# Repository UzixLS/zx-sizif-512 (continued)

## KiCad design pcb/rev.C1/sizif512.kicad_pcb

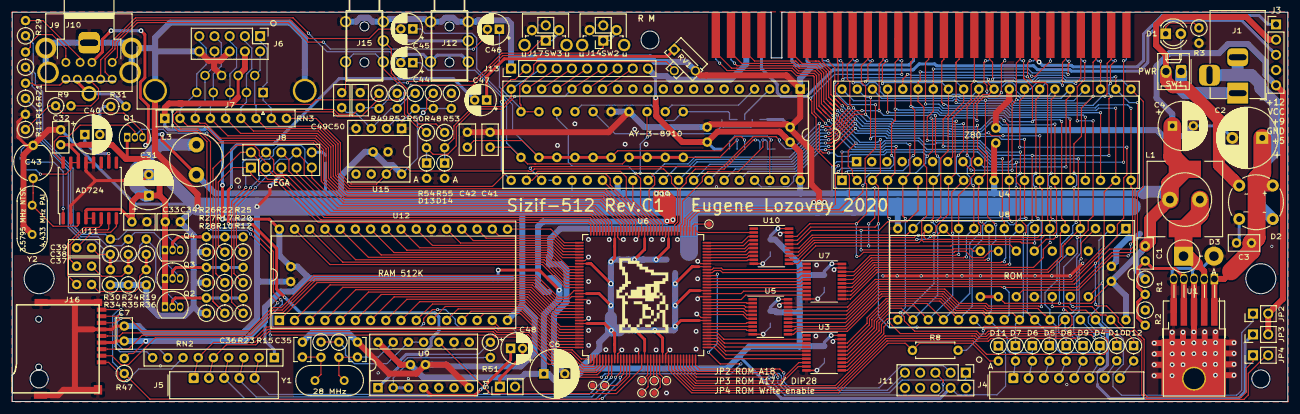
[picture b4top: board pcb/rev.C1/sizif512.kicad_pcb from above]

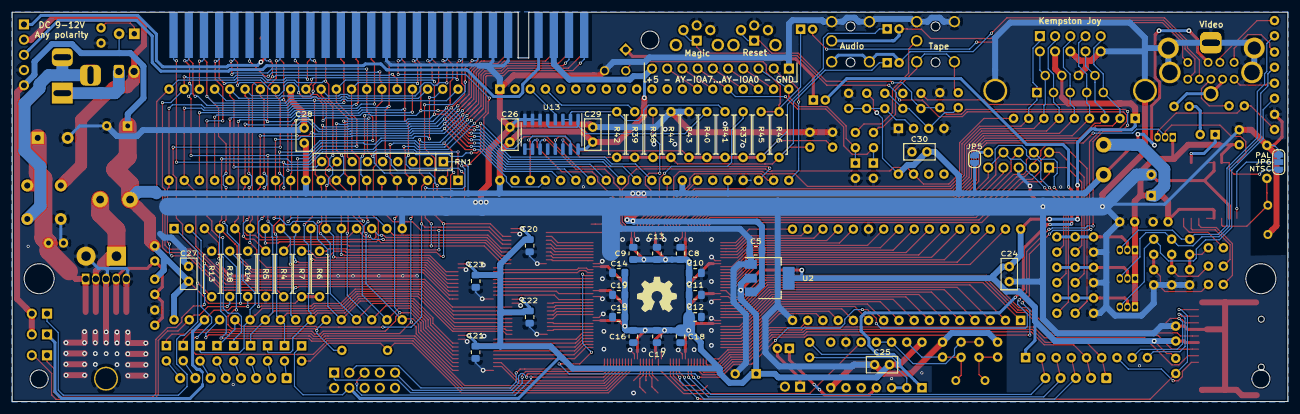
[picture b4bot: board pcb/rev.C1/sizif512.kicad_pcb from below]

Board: 2 copper layers, 213.0 x 65.0 mm, 186 parts (47 on the bottom side), 235 nets.

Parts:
C1: 15n; C_Disc_D5.0mm_W2.5mm_P2.50mm
C2: 470u/25V; CP_Radial_D10.0mm_P5.00mm
C3, C7, C24, C25, C26, C27, C28, C29, C30, C32, C33, C34, C37, C38, C39, C49, C50: 100n; C_Disc_D5.0mm_W2.5mm_P2.50mm
C4, C6, C31: 220u/16V; CP_Radial_D8.0mm_P3.50mm
C5, C8, C9, C10, C11, C12, C13, C14, C15, C16, C17, C19, C20, C21, C22, C23: 100n; C_0805_2012Metric_Pad1.15x1.40mm_HandSolder
C18: 10n; C_0805_2012Metric_Pad1.15x1.40mm_HandSolder
C35, C36: 22p; C_Disc_D3.8mm_W2.6mm_P2.50mm
C40: 220u/16V; CP_Radial_D6.3mm_P2.50mm
C41, C42: 4.7n; C_Disc_D5.0mm_W2.5mm_P2.50mm
C43: 30p; C_Trim_D6.3mm_P5.50mm
C44, C45, C46, C48: 10u/16V; CP_Radial_D5.0mm_P2.00mm
C47: 1u; CP_Radial_D5.0mm_P2.00mm
D1: LED; LED_D4.0mm
D2: 2W10; Diode_Bridge_Round_D10.0mm
D3: 1N5820; D_DO-201AD_P5.08mm_Vertical_AnodeUp
D4, D5, D6, D7, D8, D9, D10, D11, D12, D13, D14: BAT85; D_DO-35_SOD27_P2.54mm_Vertical_AnodeUp
H1, H2: MountingHole; MountingHole_5mm
H3, H4, H5: MountingHole; MountingHole_3mm
J1: DS-210; BarrelJack_Horizontal
J2: Conn_02x28_Row_Letter_First; ZX_EDGE
J3: PinHeader; PinHeader_1x05_P2.54mm_Vertical
J4: DS1020-08; FFC_FPC_1x08
J5: DS1020-05; FFC_FPC_1x05
J6, J8, J11: PinHeader; PinHeader_2x05_P2.54mm_Vertical
J7: DB9-M; DSUB-9_Male_Horizontal_P2.77x2.84mm_EdgePinOffset4.94mm_Hou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
J9: Mini-DIN-9; minidin-9
J10: RCJ-014; CUI_RCJ-01X-WIDE
J12, J15: PJ-313
J13: PinHeader; PinHeader_1x10_P2.54mm_Vertical
J14, J17: PinHeader; PinHeader_2x01_P2.54mm_Vertical
J16: MEM2055-00-190-01-A; GCT-MEM2055-00-190-01-A
JP2, JP3, JP4: Jumper; PinHeader_1x02_P2.54mm_Vertical
JP5: SolderJumper_2_Open; SolderJumper-2_P1.3mm_Open_RoundedPad1.0x1.5mm
JP6: Jumper_3_Bridged12; SolderJumper-3_P1.3mm_Bridged12_RoundedPad1.0x1.5mm_NumberL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
L1: 68uH/2A; L_Radial_D8.7mm_P5.00mm_Fastron_07HCP
L2: 68uH/2A; L_12x12mm_H8mm
L3: 220u/0.2A; L_Radial_D8.7mm_P5.00mm_Fastron_07HCP
LOGO1: graphic; black-mage2
LOGO2: Logo_Open_Hardware_Small; OSHW-Symbol_6.7x6mm_SilkScreen
LS1: PinHeader; PinHeader_1x02_P2.54mm_Vertical
Q1, Q2, Q3, Q4: BC549B; TO-92_Inline
R1, R12, R20, R25: 3k; R_Axial_DIN0207_L6.3mm_D2.5mm_P2.54mm_Vertical
R2, R48, R53: 1k; R_Axial_DIN0207_L6.3mm_D2.5mm_P2.54mm_Vertical
R3: 470; R_Axial_DIN0207_L6.3mm_D2.5mm_P2.54mm_Vertical
R4, R8: 470; R_Axial_DIN0207_L6.3mm_D2.5mm_P7.62mm_Horizontal
R5, R13, R14, R18: 10k; R_Axial_DIN0207_L6.3mm_D2.5mm_P7.62mm_Horizontal
R6, R7, R41, R42: 2k; R_Axial_DIN0207_L6.3mm_D2.5mm_P7.62mm_Horizontal
R9, R11, R23: 270; R_Axial_DIN0207_L6.3mm_D2.5mm_P2.54mm_Vertical
R10, R17, R22, R26, R27, R28: 1.5k; R_Axial_DIN0207_L6.3mm_D2.5mm_P2.54mm_Vertical
R15, R52: 1M; R_Axial_DIN0207_L6.3mm_D2.5mm_P2.54mm_Vertical
R16, R19, R21, R24, R29, R30: 68; R_Axial_DIN0207_L6.3mm_D2.5mm_P2.54mm_Vertical
R31, R34, R35, R36: 75; R_Axial_DIN0207_L6.3mm_D2.5mm_P2.54mm_Vertical
R37, R38, R39, R40, R43, R44: 1k; R_Axial_DIN0207_L6.3mm_D2.5mm_P7.62mm_Horizontal
R45, R46: 4.7k; R_Axial_DIN0207_L6.3mm_D2.5mm_P7.62mm_Horizontal
R47, R50, R51, R54, R55: 10k; R_Axial_DIN0207_L6.3mm_D2.5mm_P2.54mm_Vertical
R49: 100k; R_Axial_DIN0207_L6.3mm_D2.5mm_P2.54mm_Vertical
RN1, RN2, RN3: 10k; R_Array_SIP9
RV1: RM063 47k; Potentiometer_Runtron_RM-063_Horizontal
SW1: Jumper; Molex_KK-254_AE-6410-02A_1x02_P2.54mm_Vertical
SW2, SW3: Button THT; SW_Tactile_SPST_Angled_PTS645Vx83-2LFS
TP1, TP2, TP3, TP4, TP5, TP6, TP7, TP8: TestPoint; TestPoint_Pad_D1.0mm
U1: LM2596T-ADJ; TO-220-263-5_Horizontal_TabDown
U2: AMS1117-3.3; SOT-223-3_TabPin2
U3, U5, U7, U10: SN74CB3T3245PW; TSSOP-20_4.4x6.5mm_P0.65mm
U4: Z84C0010PEC; DIP-40_W15.24mm_Socket
U6: EPM1270T144; LQFP-144_20x20mm_P0.5mm
U8: SST39SF040; DIP-32_W15.24mm_Socket
U9: 74HCU04; DIP-14_W7.62mm_Socket
U11: AD724; SOIC-16W_7.5x10.3mm_P1.27mm
U12: AS6C4008-55PCN; DIP-32_W15.24mm_Socket
U13: 74HCT4053D; SOIC-16_3.9x9.9mm_P1.27mm
U14: AY-3-8910; DIP-40_W15.24mm_Socket
U15: LM311N; DIP-8_W7.62mm_Socket
Y1: 28 MHz; Crystal_HC49-U_Vertical
Y2: 4.433 MHz; Crystal_HC49-U_Vertical

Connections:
+3V3: C6.1, C7.2, C8.1, C9.1, C10.1, C11.1, C12.1, C13.1, C14.1, C15.1, C16.1, C17.1, C18.1, C19.1, C20.1, C21.1, C22.1, C23.1, C24.2, C25.2, D11.1, J6.4, J7.7, J11.4, J16.4, R47.2, R49.1, RN2.1, RN3.1, U2.2, U3.20, U5.20, U6.9, U6.19, U6.25, U6.46, U6.56, U6.64, U6.82, U6.90, U6.100, U6.116, U6.126, U6.136, U7.20, U9.14, U10.20, U12.32
+5V: C1.1, C4.1, C5.2, C26.2, C27.2, C28.2, C29.2, C30.2, D1.2, J2.A3, J3.5, J9.2, J13.10, JP2.2, JP3.2, JP5.1, L1.2, L2.2, L3.1, R1.1, R6.1, R7.2, R18.1, R48.1, RN1.1, U2.3, U4.11, U8.32, U13.16, U14.25, U14.28, U14.40, U15.8
+5VA: C31.1, C32.2, C33.2, C34.2, JP6.3, L3.2, Q1.1, Q2.1, Q3.1, Q4.1, U11.4, U11.5, U11.14, U11.15
+9V: J2.A4, J3.3
+12V: J2.B22, J3.1
/A0: J2.A9, U4.30, U7.18, U8.12
/A1: J2.A10, U4.31, U7.17, U8.11
/A2: J2.A11, U4.32, U7.16, U8.10
/A3: J2.A12, U4.33, U7.15, U8.9
/A4: J2.A24, U4.34, U7.14, U8.8
/A5: J2.A23, U4.35, U8.7, U10.12
/A6: J2.A22, U4.36, U7.13, U8.6
/A7: J2.A21, U4.37, U7.12, U8.5
/A8: D4.1, J2.B26, U4.38, U5.13, U8.27
/A9: D5.1, J2.A27, U4.39, U5.12, U8.26
/A10: D6.1, J2.B27, U3.18, U4.40, U8.23
/A11: D7.1, J2.A28, U4.1, U5.11, U8.25
/A12: D8.1, J2.A2, U4.2, U7.11, U8.4
/A13: D9.1, J2.B2, U4.3, U8.28, U10.17
/A14: D10.1, J2.A1, U3.11, U4.4
/A15: D12.1, J2.B1, U3.13, U4.5
/AY_ABC: U6.78, U13.9, U13.10
/AY_BC1: U6.86, U14.29
/AY_BDIR: U6.89, U14.27
/AY_CLK: U6.88, U14.22
/AY_MONO: U6.79, U13.11
/Blue0: J8.8, R25.1, U6.102
/Blue1: J8.1, R22.1, U6.108
/CLK28: U6.18, U9.10
/CLKCPU: R6.2, U4.6, U10.16
/Csync: Q1.2, U6.98, U11.16
/D0: J2.B6, U4.14, U8.13, U10.13, U14.37
/D1: J2.B7, U4.15, U8.14, U10.14, U14.36
/D2: J2.B8, U4.12, U8.15, U10.15, U14.35
/D3: J2.B11, U3.12, U4.8, U8.17, U14.34
/D4: J2.B12, U3.14, U4.7, U8.18, U14.33
/D5: J2.B10, U3.15, U4.9, U8.19, U14.32
/D6: J2.B9, U3.16, U4.10, U8.20, U14.31
/D7: J2.B3, U3.17, U4.13, U8.21, U14.30
/Green0: J8.9, R20.1, U6.101
/Green1: J8.2, R17.1, U6.107
/Hsync: J8.7, U6.103
/KA8: D4.2, J4.6
/KA9: D5.2, J4.3
/KA10: D6.2, J4.2
/KA11: D7.2, J4.1
/KA12: D8.2, J4.4
/KA13: D9.2, J4.5
/KA14: D10.2, J4.7
/KA15: D12.2, J4.8
/KD0: J5.1, RN2.6, U6.4
/KD1: J5.2, RN2.5, U6.5
/KD2: J5.3, RN2.4, U6.11
/KD3: J5.4, RN2.3, U6.8
/KD4: J5.5, RN2.2, U6.7
/RA14: U6.30, U8.29
/RA15: U6.29, U8.3
/RA16: U6.28, U8.2
/RX: C49.2, J15.T, R54.1
/Red0: J8.4, R12.1, U6.105
/Red1: J8.3, R10.1, U6.106
/SD_CD: J16.9, R47.1, U6.12
/SD_CS: J16.2, U6.3
/SD_DAT1: J16.8, RN2.9
/SD_DAT2: J16.1, RN2.7
/SD_MISO: J16.7, RN2.8, U6.125
/SD_MOSI: J16.3, U6.129
/SD_SCK: J16.5, U6.127
/SND_DAC_L: R38.2, U6.84
/SND_DAC_R: R37.2, U6.85
/SND_L: C44.2, J9.8, J12.T
/SND_MONO: C46.2, J9.6
/SND_R: C45.2, J9.9, J12.R
/TAPE_IN0: RN3.9, U6.80, U15.7
/TCK: J11.1, U6.35
/TDI: J11.9, U6.34
/TDO: J11.3, U6.36
/TMS: J11.5, U6.33
/TX: J15.R, R55.1
/VA0: U6.143, U12.12
/VA1: U6.142, U12.11
/VA2: U6.141, U12.10
/VA3: U6.140, U12.9
/VA4: U6.139, U12.8
/VA5: U6.138, U12.7
/VA6: U6.137, U12.6
/VA7: U6.134, U12.5
/VA8: U6.120, U12.27
/VA9: U6.119, U12.26
/VA10: U6.114, U12.23
/VA11: U6.118, U12.25
/VA12: U6.133, U12.4
/VA13: U6.121, U12.28
/VA14: U6.132, U12.3
/VA15: U6.124, U12.31
/VA16: U6.131, U12.2
/VA17: U6.130, U12.1
/VA18: U6.123, U12.30
/VD0: U6.144, U12.13
/VD1: U6.1, U12.14
/VD2: U6.2, U12.15
/VD3: U6.109, U12.17
/VD4: U6.110, U12.18
/VD5: U6.111, U12.19
/VD6: U6.112, U12.20
/VD7: U6.113, U12.21
/VID_B: J9.1, R29.2
/VID_COMP: J9.4, J10.1, R31.2
/VID_G: J9.3, R21.2
/VID_R: J9.7, R16.2
/VID_SYNC: J9.5, R9.2
/Vsync: J8.6, U6.104
/xA0: U6.63, U7.2
/xA1: U6.62, U7.3
/xA2: U6.60, U7.4
/xA3: U6.59, U7.5
/xA4: U6.58, U7.6
/xA5: U6.67, U10.8
/xA6: U6.57, U7.7
/xA7: U6.55, U7.8
/xA8: U5.7, U6.45
/xA9: U5.8, U6.44
/xA10: U3.2, U6.42
/xA11: U5.9, U6.43
/xA12: U6.53, U7.9
/xA13: U6.72, U10.3
/xA14: U3.9, U6.31
/xA15: U3.7, U6.37
/xCLKCPU: U6.71, U10.4
/xD0: U6.68, U10.7
/xD1: U6.69, U10.6
/xD2: U6.70, U10.5
/xD3: U3.8, U6.32
/xD4: U3.6, U6.38
/xD5: U3.5, U6.39
/xD6: U3.4, U6.40
/xD7: U3.3, U6.41
/~BUSACK: J2.A26, U4.23
/~BUSRQ: J2.A19, RN1.9, U4.25
/~CLKCPU: J2.A8, R7.1, U10.18
/~HALT: J2.B15, U4.18
/~INT: J2.B13, U4.16, U6.77
/~IORQ: J2.B17, R4.2, U4.20
/~IORQGE: J2.A13, R4.1, U10.11
/~JOY_B1: J6.2, J7.6, RN3.7, U6.91
/~JOY_B2: J6.8, J7.9, RN3.3, U6.96
/~JOY_B3: J6.9, J7.5, RN3.2, U6.97
/~JOY_DOWN: J6.3, J7.2, RN3.6, U6.93
/~JOY_LEFT: J6.5, J7.3, RN3.5, U6.94
/~JOY_RIGHT: J6.7, J7.4, RN3.4, U6.95
/~JOY_UP: J6.1, J7.1, RN3.8, U6.87
/~M1: J2.B24, U4.27, U5.14
/~MREQ: J2.B16, U4.19, U5.18
/~NMI: J2.B14, U4.17, U6.76
/~RD: J2.B18, RN1.7, U4.21, U5.15, U8.24
/~RFSH: J2.B25, U4.28, U5.17
/~ROMCS: D11.2, R8.2, U6.27
/~ROMCSB: J2.A25, R8.1, U8.22
/~RSTCPU: J2.A20, R5.1, U4.26, U6.75, U14.23
/~VRD: U6.117, U12.24
/~VWR: U6.122, U12.29
/~WAIT: J2.B21, RN1.8, U4.24
/~WR: J2.B19, JP4.1, U4.22, U5.16
/~xCLKCPU_IO73: U6.73, U10.2
/~xIORQGE: U6.66, U10.9
/~xM1: U5.6, U6.48
/~xMREQ: U5.2, U6.52
/~xRD: U5.5, U6.49
/~xRFSH: U5.3, U6.51
/~xWR: U5.4, U6.50
GND: C2.2, C3.2, C4.2, C5.1, C6.2, C7.1, C8.2, C9.2, C10.2, C11.2, C12.2, C13.2, C14.2, C15.2, C16.2, C17.2, C18.2, C19.2, C20.2, C21.2, C22.2, C23.2, C24.1, C25.1, C26.1, C27.1, C28.1, C29.1, C30.1, C31.2, C32.1, C33.1, C34.1, C35.1, C36.1, C41.2, C42.2, C43.2, C50.1, D2.1, D3.2, D13.2, D14.2, J2.A6, J2.A7, J2.A14, J3.4, J6.6, J6.10, J7.0, J7.8, J8.5, J9.0, J10.2, J11.2, J11.10, J12.S, J13.1, J14.2, J15.S, J16.6, J16.10, J17.2, JP6.1, LS1.2, R2.1, R3.2, R5.2, R11.2, R13.1, R14.1, R26.1, R27.1, R28.1, R34.1, R35.1, R36.1, R43.2, R44.2, R52.1, R53.1, RV1.3, SW2.1, SW3.1, U1.3, U1.5, U2.1, U3.10, U3.19, U4.29, U5.10, U5.19, U6.10, U6.17, U6.26, U6.47, U6.54, U6.65, U6.83, U6.92, U6.99, U6.115, U6.128, U6.135, U7.10, U7.19, U8.16, U9.5, U9.7, U9.9, U10.10, U10.19, U11.2, U11.12, U11.13, U12.16, U12.22, U13.6, U13.7, U13.8, U14.1, U14.24, U15.1, U15.4, Y2.2
unnamed: C1.2, R1.2, R2.2, U1.4
unnamed: C2.1, C3.1, D2.3, U1.1
unnamed: C35.2, R15.2, U9.13, Y1.2
unnamed: C36.2, R23.2, Y1.1
unnamed: C37.1, R19.1, R36.2
unnamed: C37.2, U11.6
unnamed: C38.1, R24.1, R35.2
unnamed: C38.2, U11.7
unnamed: C39.1, R30.1, R34.2
unnamed: C39.2, U11.8
unnamed: C40.1, U11.10
unnamed: C40.2, R31.1
unnamed: C41.1, C44.1, R38.1, R39.1, R42.1, R44.1, R46.1, U13.14
unnamed: C42.1, C45.1, R37.1, R40.1, R41.1, R43.1, R45.1, U13.13
unnamed: C43.1, U11.3, Y2.1
unnamed: C46.1, R45.2, R46.2, RV1.2
unnamed: C47.1, RV1.1
unnamed: C47.2, R51.1, U9.1
unnamed: C48.1, U9.4
unnamed: C48.2, LS1.1
unnamed: C49.1, R50.1, R52.2, U15.3
unnamed: D1.1, R3.1
unnamed: D2.2, J1.2, J1.3
unnamed: D3.1, L1.1, L2.1, U1.2
unnamed: D13.1, J13.7, R54.2, U14.16
unnamed: D14.1, J13.3, R55.2, U14.20
unnamed: J1.1, SW1.1
unnamed: J8.10, JP5.2
unnamed: J13.2, U14.21
unnamed: J13.4, U14.19
unnamed: J13.5, U14.18
unnamed: J13.6, U14.17
unnamed: J13.8, U14.15
unnamed: J13.9, U14.14
unnamed: JP2.1, R13.2, U8.1
unnamed: JP3.1, R14.2, U8.30
unnamed: JP4.2, R18.2, U8.31
unnamed: JP6.2, U11.1
unnamed: Q1.3, R9.1, R11.1
unnamed: Q2.2, R10.2, R12.2, R28.2
unnamed: Q2.3, R16.1, R19.2
unnamed: Q3.2, R17.2, R20.2, R27.2
unnamed: Q3.3, R21.1, R24.2
unnamed: Q4.2, R22.2, R25.2, R26.2
unnamed: Q4.3, R29.1, R30.2
unnamed: R15.1, R23.1, U9.11, U9.12
unnamed: R39.2, U14.4
unnamed: R40.2, U13.1, U13.5
unnamed: R41.2, R42.2, U13.2, U13.3
unnamed: R48.2, R50.2, R53.2, U15.2
unnamed: R51.2, U9.2, U9.3
unnamed: TP1.1, U6.74
unnamed: TP2.1, U6.13
unnamed: TP3.1, U6.14
unnamed: TP4.1, U6.20
unnamed: TP5.1, U6.21
unnamed: TP6.1, U6.22
unnamed: TP7.1, U6.23
unnamed: TP8.1, U6.24
unnamed: U13.4, U14.3
unnamed: U13.15, U14.38
VCC: D2.4, J3.2, SW1.2
~MAGIC: J14.1, SW2.2, U6.6
~RST: C50.2, J17.1, R49.2, SW3.2, U6.61

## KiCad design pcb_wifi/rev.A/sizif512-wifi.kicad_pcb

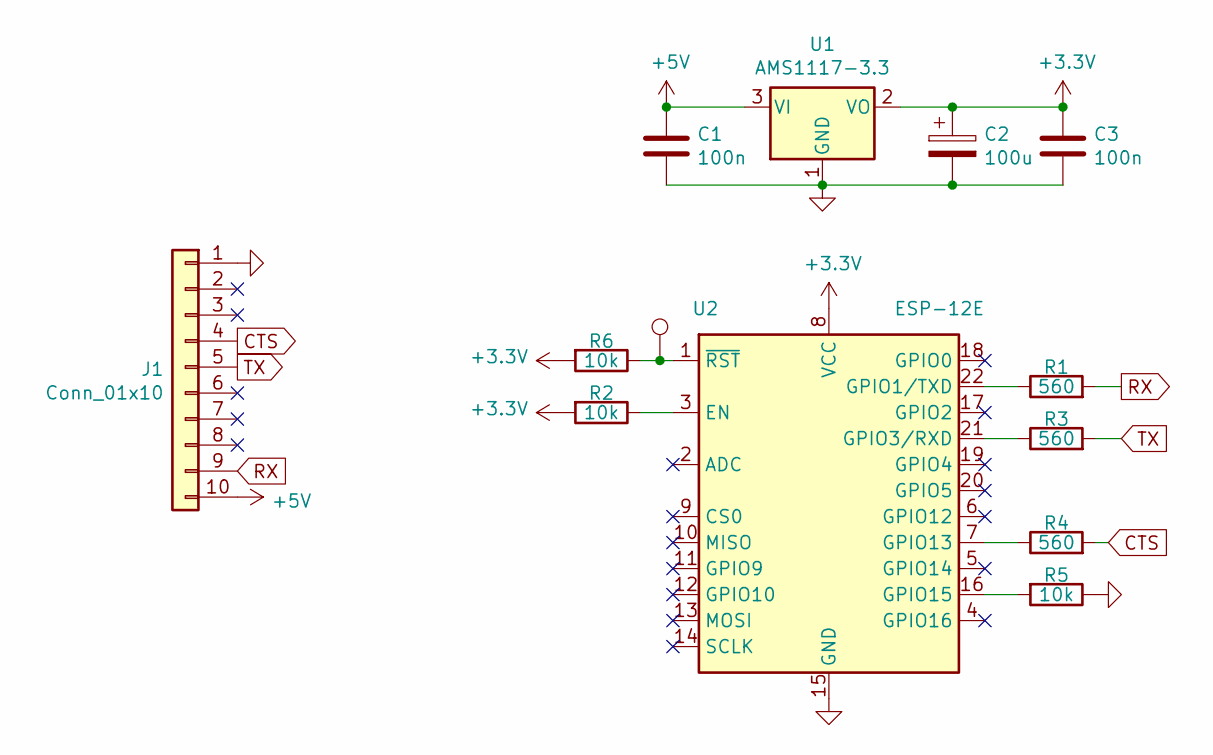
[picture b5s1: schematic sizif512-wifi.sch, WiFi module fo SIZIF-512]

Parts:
C1, C3: 100n; C_0805_2012Metric_Pad1.15x1.40mm_HandSolder
C2: 100u; C_2010_5025Metric_Pad1.52x2.65mm_HandSolder
J1: Conn_01x10; PinSocket_1x10_P2.54mm_Vertical
R1, R3, R4: 560; C_0805_2012Metric_Pad1.15x1.40mm_HandSolder
R2, R5, R6: 10k; C_0805_2012Metric_Pad1.15x1.40mm_HandSolder
TP1: TestPoint; Pin_D0.7mm_L6.5mm_W1.8mm_FlatFork
U1: AMS1117-3.3; SOT-223-3_TabPin2
U2: ESP-12E; ESP-12E_SMD

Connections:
+3V3: C2.1, C3.1, R2.2, R6.2, U1.2 (VO), U2.8 (VCC)
+5V: C1.1, J1.10, U1.3 (VI)
CTS: J1.4, R4.2
GND: C1.2, C2.2, C3.2, J1.1, R5.1, U1.1 (GND), U2.15 (GND)
unnamed: R1.1, U2.22 (GPIO1/TXD)
unnamed: R2.1, U2.3 (EN)
unnamed: R3.1, U2.21 (GPIO3/RXD)
unnamed: R4.1, U2.7 (GPIO13)
unnamed: R5.2, U2.16 (GPIO15)
unnamed: R6.1, TP1.1, U2.1 (~RST)
RX: J1.9, R1.2
TX: J1.5, R3.2

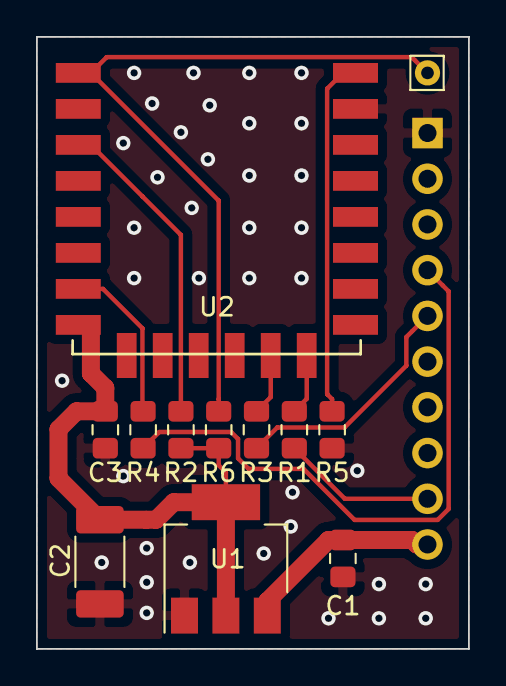
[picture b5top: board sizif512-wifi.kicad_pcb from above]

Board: 2 copper layers, 24.0 x 34.0 mm, 13 parts (1 on the bottom side), 12 nets.

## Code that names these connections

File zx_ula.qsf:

# -------------------------------------------------------------------------- #
#
# Copyright (C) 1991-2009 Altera Corporation
# Your use of Altera Corporation's design tools, logic functions 
# and other software and tools, and its AMPP partner logic 
# functions, and any output files from any of the foregoing 
# (including device programming or simulation files), and any 
# associated documentation or information are expressly subject 
# to the terms and conditions of the Altera Program License 
# Subscription Agreement, Altera MegaCore Function License 
# Agreement, or other applicable license agreement, including, 
# without limitation, that your use is for the sole purpose of 
# programming logic devices manufactured by Altera and sold by 
# Altera or its authorized distributors.  Please refer to the 
# applicable agreement for further details.
#
# -------------------------------------------------------------------------- #
#
# Quartus II
# Version 9.0 Build 235 06/17/2009 Service Pack 2 SJ Web Edition
# Date created = 08:15:12  April 28, 2019
#
# -------------------------------------------------------------------------- #
#
# Notes:
#
# 1) The default values for assignments are stored in the file:
#		zx_ula_assignment_defaults.qdf
#    If this file doesn't exist, see file:
#		assignment_defaults.qdf
#
# 2) Altera recommends that you do not modify this file. This
#    file is updated automatically by the Quartus II software
#    and any changes you make may be lost or overwritten.
#
# -------------------------------------------------------------------------- #


set_global_assignment -name FAMILY MAX3000A
set_global_assignment -name DEVICE "EPM3256ATC144-10"
set_global_assignment -name TOP_LEVEL_ENTITY zx_ula
set_global_assignment -name ORIGINAL_QUARTUS_VERSION "9.0 SP2"
set_global_assignment -name PROJECT_CREATION_TIME_DATE "08:15:12  APRIL 28, 2019"
set_global_assignment -name LAST_QUARTUS_VERSION "9.0 SP2"
set_global_assignment -name USE_GENERATED_PHYSICAL_CONSTRAINTS OFF -section_id eda_blast_fpga
set_global_assignment -name MAX7000_DEVICE_IO_STANDARD "3.3-V LVTTL"
set_location_assignment PIN_36 -to n_int
set_location_assignment PIN_29 -to n_iorq
set_location_assignment PIN_34 -to n_m1
set_location_assignment PIN_28 -to n_mreq
set_location_assignment PIN_27 -to n_rfsh
set_location_assignment PIN_6 -to n_vwr
set_location_assignment PIN_72 -to r
set_location_assignment PIN_127 -to rst_n
set_location_assignment PIN_60 -to tape_out
set_location_assignment PIN_25 -to va[16]
set_location_assignment PIN_30 -to va[15]
set_location_assignment PIN_31 -to va[14]
set_location_assignment PIN_11 -to va[13]
set_location_assignment PIN_12 -to va[12]
set_location_assignment PIN_14 -to va[11]
set_location_assignment PIN_15 -to va[10]
set_location_assignment PIN_16 -to va[9]
set_location_assignment PIN_18 -to va[8]
set_location_assignment PIN_8 -to va[7]
set_location_assignment PIN_5 -to va[6]
set_location_assignment PIN_2 -to va[5]
set_location_assignment PIN_1 -to va[4]
set_location_assignment PIN_10 -to va[1]
set_location_assignment PIN_9 -to va[0]
set_location_assignment PIN_39 -to vd[7]
set_location_assignment PIN_40 -to vd[6]
set_location_assignment PIN_38 -to vd[4]
set_location_assignment PIN_37 -to vd[2]
set_location_assignment PIN_32 -to vd[0]
set_global_assignment -name MISC_FILE "E:/ws/quartus/zx_ula/zx_ula.dpf"
set_global_assignment -name VERILOG_INPUT_VERSION SYSTEMVERILOG_2005
set_global_assignment -name VERILOG_SHOW_LMF_MAPPING_MESSAGES OFF
set_global_assignment -name MAX7000_OPTIMIZATION_TECHNIQUE AREA
set_global_assignment -name FMAX_REQUIREMENT "14.4 MHz"
set_global_assignment -name FMAX_REQUIREMENT "14.4 MHz" -section_id clk14
set_location_assignment PIN_23 -to va[18]
set_location_assignment PIN_7 -to va[17]
set_location_assignment PIN_54 -to n_iorqge_i
set_location_assignment PIN_53 -to n_iorqge_o
set_global_assignment -name FMAX_REQUIREMENT "7.156 MHz" -section_id clkcpu
set_instance_assignment -name CLOCK_SETTINGS clkcpu -to clkcpu
set_location_assignment PIN_45 -to a1
set_location_assignment PIN_35 -to n_nmi
set_global_assignment -name AUTO_RESOURCE_SHARING OFF
set_global_assignment -name AUTO_LCELL_INSERTION OFF
set_location_assignment PIN_47 -to n_rstcpu
set_global_assignment -name INCREMENTAL_COMPILATION OFF
set_location_assignment PIN_63 -to n_joy_b1
set_location_assignment PIN_69 -to n_joy_b2
set_location_assignment PIN_68 -to n_joy_b3
set_location_assignment PIN_65 -to n_joy_down
set_location_assignment PIN_66 -to n_joy_left
set_location_assignment PIN_67 -to n_joy_right
set_location_assignment PIN_62 -to n_joy_up
set_location_assignment PIN_116 -to kd[0]
set_location_assignment PIN_113 -to kd[1]
set_location_assignment PIN_121 -to kd[2]
set_location_assignment PIN_120 -to kd[3]
set_location_assignment PIN_119 -to kd[4]
set_location_assignment PIN_55 -to tape_in
set_location_assignment PIN_78 -to fd_cswg
set_location_assignment PIN_106 -to fd_dden
set_location_assignment PIN_92 -to fd_disk0
set_location_assignment PIN_86 -to fd_disk1
set_location_assignment PIN_103 -to fd_drq
set_location_assignment PIN_90 -to fd_hlt
set_location_assignment PIN_102 -to fd_intr
set_location_assignment PIN_97 -to fd_rawr
set_location_assignment PIN_98 -to fd_motor
set_location_assignment PIN_96 -to fd_rclk
set_location_assignment PIN_84 -to fd_rdat
set_location_assignment PIN_83 -to fd_rst
set_location_assignment PIN_88 -to fd_side1
set_location_assignment PIN_81 -to fd_sl
set_location_assignment PIN_82 -to fd_sr
set_location_assignment PIN_99 -to fd_tr43
set_location_assignment PIN_19 -to ra[14]
set_location_assignment PIN_21 -to ra[15]
set_location_assignment PIN_22 -to ra[16]
set_location_assignment PIN_91 -to fd_index
set_location_assignment PIN_79 -to vsync
set_location_assignment PIN_80 -to hsync
set_location_assignment PIN_125 -to clk32
set_global_assignment -name FMAX_REQUIREMENT "32 MHz" -section_id clk32
set_instance_assignment -name CLOCK_SETTINGS clk32 -to clk32
set_global_assignment -name FMAX_REQUIREMENT "8 MHz" -section_id clk8
set_global_assignment -name FMAX_REQUIREMENT "4 MHz" -section_id clk4
set_location_assignment PIN_41 -to ay_bc1
set_location_assignment PIN_42 -to ay_bdir
set_location_assignment PIN_43 -to ay_abc
set_location_assignment PIN_44 -to a0
set_location_assignment PIN_46 -to a14
set_location_assignment PIN_48 -to a15
set_location_assignment PIN_49 -to ay_clk
set_location_assignment PIN_56 -to beeper
set_location_assignment PIN_61 -to snd
set_location_assignment PIN_70 -to i
set_location_assignment PIN_71 -to g
set_location_assignment PIN_74 -to b
set_location_assignment PIN_75 -to csync
set_location_assignment PIN_87 -to fd_wdat
set_location_assignment PIN_93 -to fd_wg_clk
set_location_assignment PIN_100 -to fd_wd
set_location_assignment PIN_101 -to fd_wf_de
set_location_assignment PIN_108 -to sd_cd
set_location_assignment PIN_109 -to sd_miso
set_location_assignment PIN_110 -to sd_sck
set_location_assignment PIN_111 -to sd_cs
set_location_assignment PIN_112 -to sd_mosi
set_location_assignment PIN_117 -to chroma[0]
set_location_assignment PIN_118 -to chroma[1]
set_location_assignment PIN_122 -to n_romcs
set_location_assignment PIN_134 -to clkcpu
set_location_assignment PIN_136 -to n_wr
set_location_assignment PIN_137 -to n_rd
set_location_assignment PIN_138 -to vd[5]
set_location_assignment PIN_139 -to vd[3]
set_location_assignment PIN_140 -to vd[1]
set_location_assignment PIN_141 -to va[2]
set_location_assignment PIN_142 -to n_vrd
set_location_assignment PIN_143 -to va[3]
set_location_assignment PIN_126 -to n_magic
set_global_assignment -name MISC_FILE "E:/ws/quartus/zx-sizif-512/zx_ula.dpf"
set_global_assignment -name MISC_FILE "Z:/zx-sizif-512/zx_ula.dpf"
set_instance_assignment -name CLOCK_SETTINGS clk8 -to "lpm_counter:wgcnt_rtl_1|dffs[1]"
set_instance_assignment -name CLOCK_SETTINGS clk4 -to "lpm_counter:wgcnt_rtl_1|dffs[2]"
set_location_assignment PIN_132 -to a13
set_global_assignment -name RESERVE_ALL_UNUSED_PINS_NO_OUTPUT_GND "AS INPUT TRI-STATED"
set_global_assignment -name OPTIMIZE_HOLD_TIMING OFF
set_global_assignment -name FITTER_EFFORT "STANDARD FIT"
set_global_assignment -name PROJECT_OUTPUT_DIRECTORY output/
set_location_assignment PIN_107 -to fd_index1
set_location_assignment PIN_128 -to clk7
set_global_assignment -name VHDL_FILE chroma_gen32.vhd
set_global_assignment -name VERILOG_FILE top.v
set_global_assignment -name VERILOG_INCLUDE_FILE util.vh
set_global_assignment -name FMAX_REQUIREMENT "7.156 MHz" -section_id clk7
set_global_assignment -name DUTY_CYCLE 40 -section_id clk7
set_instance_assignment -name CLOCK_SETTINGS clk7 -to clk7

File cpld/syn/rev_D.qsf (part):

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set_global_assignment -name POWER_PRESET_COOLING_SOLUTION "NO HEAT SINK WITH STILL AIR"

set_location_assignment PIN_1 -to r[1]
set_location_assignment PIN_2 -to vsync
set_location_assignment PIN_3 -to hsync
set_location_assignment PIN_6 -to sd_cd
set_location_assignment PIN_7 -to sd_miso
set_location_assignment PIN_8 -to sd_sck
set_location_assignment PIN_11 -to sd_mosi
set_location_assignment PIN_12 -to sd_cs
set_location_assignment PIN_13 -to kd[4]
set_location_assignment PIN_14 -to kd[3]
set_location_assignment PIN_15 -to kd[2]
set_location_assignment PIN_16 -to kd[1]
set_location_assignment PIN_18 -to kd[0]
set_location_assignment PIN_22 -to bus0
set_location_assignment PIN_23 -to bus1
set_location_assignment PIN_24 -to n_romcs
set_location_assignment PIN_27 -to ra[17]
set_location_assignment PIN_28 -to ra[16]
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set_location_assignment PIN_68 -to xd[0]
set_location_assignment PIN_69 -to xd[1]
set_location_assignment PIN_70 -to xd[2]
set_location_assignment PIN_71 -to clkcpu
set_location_assignment PIN_72 -to xa[13]
set_location_assignment PIN_73 -to n_int
set_location_assignment PIN_74 -to n_nmi
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set_location_assignment PIN_77 -to plus3_mtr
set_location_assignment PIN_78 -to plus3_dwr
set_location_assignment PIN_79 -to plus3_drd
set_location_assignment PIN_80 -to ay_abc
set_location_assignment PIN_81 -to ay_mono
set_location_assignment PIN_84 -to n_magic
set_location_assignment PIN_85 -to snd_l
set_location_assignment PIN_86 -to tape_in
set_location_assignment PIN_87 -to ay_bc1
set_location_assignment PIN_88 -to ay_bdir
set_location_assignment PIN_89 -to snd_r
set_location_assignment PIN_91 -to clk28
set_location_assignment PIN_93 -to ay_clk
set_location_assignment PIN_95 -to n_joy_up
set_location_assignment PIN_96 -to n_joy_b1
set_location_assignment PIN_97 -to n_joy_down
set_location_assignment PIN_98 -to joy_sel
set_location_assignment PIN_101 -to n_joy_left
set_location_assignment PIN_102 -to vd[3]
set_location_assignment PIN_103 -to n_joy_right
set_location_assignment PIN_104 -to vd[4]
set_location_assignment PIN_105 -to n_joy_b2
set_location_assignment PIN_106 -to vd[6]
set_location_assignment PIN_107 -to csync
set_location_assignment PIN_108 -to vd[5]
set_location_assignment PIN_109 -to vd[7]
set_location_assignment PIN_110 -to va[10]
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
set_global_assignment -name USE_CONFIGURATION_DEVICE ON
set_global_assignment -name RESERVE_ALL_UNUSED_PINS "AS INPUT TRI-STATED WITH WEAK PULL-UP"
set_location_assignment PIN_4 -to ps2_clk
set_location_assignment PIN_5 -to ps2_dat
set_instance_assignment -name WEAK_PULL_UP_RESISTOR ON -to ps2_clk
set_instance_assignment -name WEAK_PULL_UP_RESISTOR ON -to ps2_dat
set_global_assignment -name SYSTEMVERILOG_FILE ../rtl/ulaplus.sv
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
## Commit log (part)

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2020-02-05 initial
2020-02-05 first versioned release
2020-02-12 add roms
2020-03-25 bdi wip
2020-04-10 clk7 wip
2020-04-15 clk14 wip
2020-04-17 vg93 clk14
2020-04-23 reorganize repository
2020-04-28 add extlock config bit to disable all extra ports
2020-04-30 fix glitches in turbo mode
2020-04-30 handle magic button
2020-04-30 add testbench
2020-04-30 enable snow
2020-05-01 add pcbs
2020-05-01 add readme and license
2020-05-01 [minor] refactor feature flags
2020-05-06 improve compatibility with modern lcd tv's
2020-05-07 fix 7ffdh port decoding for better compatibility
2020-05-07 delay nmi signal relative to int
    This fixes Jan Bobrowski's btime's crash on return from esxdos nmi
    handler. I hope this commit doesn't break something else.
2020-05-07 fix pentagon timings
2020-05-09 fix crash if magic button was pressed while esxdos active
2020-05-17 fix covox
2020-05-17 update rev.A pcb
2020-05-17 add rev.B (abandoned) and rev.C (wip) pcbs
2020-05-17 readme: fix for github
2020-05-22 pcb rev.C: minor layout changes
2020-05-22 add #dffd d4 bit for nsid_emu by NS
2020-05-22 cpld fw: minor refactor
2020-05-23 cpld fw: fix #dffd_d4 divmmc compatibility
2020-05-23 cpld fw: add #dffd d3 bit for pac-man emulator
2020-05-31 update readme with links to youtube
2020-07-06 [minor] update kicad project file
2020-07-06 add cpld firmware for rev.C (initial version)
2020-07-06 [minor]: fix kicad project files
2020-07-06 add pcb rev.C1
2020-07-07 add soundrive
2020-07-07 some minor cleanup
2020-07-10 initial ulaplus implementation (wip)
2020-07-18 pcb rev.C1: minor values change
    Video circuit tuning:
    R10, R17, R22, R26, R27, R27: 1.5k
    R12, R20, R25: 3k
    C43: 30p (wider range is better)
    Q1, Q2, Q3, Q4: BC549B (low noise, less amplification)
    Exclude 2.2k value from BOM:
2020-07-18 cpld: finish ulaplus
    EGA output is broken by new video code (because of Z-states on pins).
    Will be fixed later.
2020-07-21 pcb rev.C1: update Y1 capacitors values for better reliability
2020-07-22 add prebuilt cpld fimware for rev.C/C1 and rom image
2020-07-22 cpld: improve compatibility with some addons (like Dandanator mini)
2020-07-26 update readme: add photos
2020-07-27 add +3 ports #1ffd, #2ffd and #3ffd
    +3 ROM isn't handled yet.
2020-08-14 git: fix crlf line endings in repository
2020-08-14 cpld: add missing reset handler for some registers
2020-08-14 cpld: refactor int generator
2020-08-14 update romset:
    add +3e-divmmc rom
    update diagrom to v50
    replace pentagon.rom with 128p-0.rom
2020-08-14 add 48K timings (beta)
    Almost everything is ok (Shock Megademo, Border Trix, Dark Star,
    Aquaplane, TEST430, etc), but there is visible border offset in Vectron
    by unknown reason.
    Also 128K timings was slightly tuned.
    Contention model still inaccurate for 48K/128K.
2020-08-14 add 14 mhz turbo mode (with waitstates)
2020-08-14 add switching between 48 alternative roms and between 128 / +3e roms
2020-08-14 force int vector to #ff
2020-08-14 testbench: fix build on linux
2020-08-14 update magic button handler
    + improve compatibility (furher testing needed)
    + play tone and flash border on key press
    + add keys for turbo14 mode, 48K timings, ay mono, +3 rom, alternative
    48 rom
    + add key to do jump to #0000 (useful for rom switching)
2020-08-23 update cpld pof image and rom image
2020-09-06 fix broken magic if magic button was hold during reset
2020-09-06 use x,y,z sega gamepad buttons as turbo a,b,c
2020-09-06 implement pause on press of sega gamepad "start" button
2020-09-06 treat mode button on sega gamepad as magic button
    This is useful for entering into Dr.Slump's NMI Navigator which have
    kempston joystick support.
2020-09-11 add sinclair joystick
2020-10-04 fix reset due to ESD impact
2020-10-04 rev.A: rewrite chroma_gen in verilog
2020-10-09 cpld: fix rst_n in testbench
2020-10-19 improve compatibility with some sd cards
2020-10-19 fix snow in 14mhz mode with ula+ active
2020-10-19 tune video timings for better look
2020-10-19 rev.A: update chroma_gen
2020-10-19 pcb: add rev.D 3d render
2020-11-18 cpld: use sd_cs signal instead of sd_miso for indication on border
2020-11-18 cpld: very tiny refactor
2020-11-18 cpld: add video output code for pcb rev.D
2020-11-18 update cpld firmware
2021-02-27 add pcb rev.D
2021-02-27 add rev.D1 gerbers, firmware, etc.
2021-02-27 cpld rename rev.C -> rev.CD
2021-02-27 add pcb rev.D1
2021-02-27 update cpld firmware to support rev.D board
2021-02-27 update readme for rev.D pcb
2021-03-23 add rom image for rev.A
2021-04-07 update README - add DivIDE
2021-04-08 gitignore, gitattributes: add kicad 6 entries
2021-04-08 add photos to git
2021-04-24 fix #7ffd port decoding; 3dos ports now available only with +3 rom
    This commit improve compatibility with bunch of software like:
    - Test 4.30
    - Eye Ache 2 by Code Busters
    - 70908 by Scoopex (trd version)
    - Void by Invaders (RU version)
2021-04-26 fix testbench
2021-05-10 refactor cpld project: split everything into modules
2021-05-10 cpld: implement ps2 keyboard driver (#3)
2021-05-13 fix leaving magic handler in 14MHz turbo mode
2021-05-13 enable clamping diodes on some cpld pins just to be safe
2021-05-14 testbench: update t80
2021-05-14 testbench: fix nmi
2021-05-14 fix reserving RAM for DivMMC (broken in commit 93bcaca)
2021-05-14 improve reliability in 14MHz mode; fix reading from nonexisting ports
2021-06-06 cpld: some minor changes
2021-06-06 ps2: handle ctrl-alt-backspace as reboot
2021-06-06 update cpld pof files
2021-06-06 update readme - add link to extension board; update roadmap
2021-06-19 ps2: don't count alt as fire key when left ctrl is hold
    for ctrl-alt-del
2021-06-19 synchronize pause to int and rfsh cycle just for safety
2021-06-19 update diagrom from v50 to v54
2021-06-19 new magic rom with menu
2021-06-19 cpld: minor stylistic refactorings
2021-06-19 cpld: support for new magic rom
2021-06-23 update readme - add links to reviews
2021-06-23 handle +3 mode with 48K ram
2021-06-23 magic: fix border when entering menu
2021-06-24 magic rom: draw boxes after initing cpld at boot
2021-06-24 magic rom: fix hot switching to +3 mode when basic48 active
2021-06-27 magic rom: fix possible crash on start
2021-06-27 magic: add covox/soundrive and ulaplus configuration
2021-06-27 cpld: fix conflict between ay and attribute port
2021-07-05 magic rom: add extension board support
2021-07-10 magic rom: slightly optimize code
2021-07-10 magic rom: disable acb panning if tsfm is enabled
2021-07-10 magic rom: mute generalsound on menu entry and restore it at exit
2021-07-10 cpld: fix rev_C build
2021-07-10 update rom and cpld pof files
2021-07-10 [minor] update readme
2021-08-15 magic: correctly handle case when there is no magic rom
    This may happens in following cases:
    1. External ROM on ZXBUS is present (ROMCSB signal is active);
    2. JP2/JP3 is installed.
2021-08-20 some stability improvements
2021-08-20 update readme - add dma tested addon
2021-09-05 update readme: add links
2021-09-05 fix unpausing after reboot by ctrl-alt-del
2021-09-09 improve pause ('f12' on ps/2 keyboard or 'start' on gamepad)
2021-09-14 magic rom: fix main_test build
2021-09-14 improve ulaplus video output
2021-09-14 rom: replace OpenSE with Looking Glass
2021-09-14 enable divmmc (esxdos OS) by magic rom on poweron; add NO-OS option
2021-09-17 fix hanging of esxdos browser after magic key double press
2021-09-17 magic rom: fix 'h' font character
2021-09-18 significantly improve classic timings
2021-09-18 replace 'timings', 'ram', 'plus3' settings with one 'machine' setting
2021-09-18 handle magic key press if initialization wasn't completed before
    This may happens i.e. with Dandanator after loading the game.
2021-09-18 add Makefile
2021-09-18 refactor memory controller
2021-09-18 add more roms
    1. add per-machine romsets
    2. add two alternative 48 basics: Looking Glass ans OpenSE
    3. add ability to boot into ZX80/ZX81 roms by holding 1 or 2 key at
    poweron
2021-09-18 add 4.4 MHz and 5.2 MHz turbo modes
2021-09-19 fix video sync glitches
2021-09-26 add support for external AY on zxbus
2021-09-27 fix #fe contention in +3 mode
2021-09-27 testbench: add Z84C0010 timings
2021-09-28 improve 14MHz turbo mode stability
2021-09-30 fix random ram errors (broken in 2b0dab1)
2021-09-30 center screen in 128/+3 timings
2021-09-30 fix io contention for classic timings
2021-10-01 fix incorrect pallete after enabling ulaplus in menu
2021-12-01 disable divmmc(esxdos) when bdi(trdos) controller connected
2021-12-01 replace divmmc no-os mode with zc
2021-12-01 implement Z-Controller (ZC) sd card controller
2021-12-01 add flash (rom) programming routines
2021-12-01 replace +3e rom to support zc
    https://github.com/nihirash/plus3e-zcontroller
2021-12-01 add negluk.rom
2021-12-02 refactor menu; add boot menu
2021-12-02 [minor] refactor menu
2021-12-03 add option to disable sd indication on border
2021-12-03 add ability to save user configuration to flash
2021-12-04 add flash id check before programming
2021-12-04 add bright boost option
2021-12-04 Makefile: fix cpld file name
2022-01-27 fix compatibility with some old ps/2 keyboards
2022-01-27 magic rom: fix 'd' font character
2022-01-27 update readme: update tested addons list
    thanks to RomanRom2 for testing
2022-02-09 magic rom: fix exiting from pause
2022-02-09 magic rom: remove sizif-xxs ifdefs
2022-02-09 fix compatibility with addons asserting RSTCPU signal (e.g. dandanator)
2022-02-16 fix kempston port decoding - add DF port for some rare games
2022-05-27 fix start button on 8bitdo gamepad
2022-06-19 fix testbench rstcpu signal
2022-06-19 update gitignore
2022-07-10 save sd card setting
2022-07-30 fix ay when turbo mode enabled
    Some ay chips (mostly early ones?) stuttered when cpu frequency (and
    control signals timings) were too fast for them.
2022-07-31 fix ps/2 sticking keys
2022-08-28 allow nmi call when divmmc's mapram in use
2022-08-30 add auto cpu frequency
    When this feature enabled:
    * Frequency sets to 14MHz on esxdos activity - for fastest loading from
    sd card;
    * Frequency sets to 3.5MHz within ~1ms after #FE port access - this
    allows to load from tape within turbo mode. Also this improves beeper
    sound effects;
2022-08-30 change ps/2 keyboard mapping
    * pause has been moved from F12 to F1
    * reboot has been assigned to F10 and F12 (but still present on
    Ctrl-Alt-Del / Ctrl-Alt-Backspace)
2022-10-01 add support for ZXKIT1 vga converter
    When ZXKIT1 setting enabled in menu:
    - Hsync on EGA header acts as Csync
    - Vsync on EGA header acts as 14MHz out
2022-10-02 add pcb rev.E
2022-10-02 add rev.E1 gerbers, pdfs, etc.
2022-10-02 add rev.E photo
2022-10-02 cpld: add support for pcb rev.E
2022-10-02 add rev.A photo
2022-10-02 add pcb rev.E1
2023-01-01 [minor] flash.asm: fix typo
2023-02-15 minor refactor
2023-02-16 add option to remap gamepad button A as UP
2023-03-01 minor refactor: export clocks instead of blink_cnt
2023-03-02 turn on additional quartus speed optimizations
2023-03-02 increase ay volume
2023-04-03 fix ula+ io contention for classic timings
    ham256.tap has been affected
2023-04-04 fix esxdos tap file loading in +3e mode
2023-04-04 add version and timestamp to rom file
2023-04-27 attribute port is now accessible only via #FF address
    this is required to prevent a bus conflict when reading ports from addon connected to zxbus
2023-05-01 correctly handle magic_map on magic button press when DivIDE addon is installed
2023-05-01 fix basic 128 crashes when divmmc is enabled
2023-10-27 refactor: rename screen->video, memcontrol->mem, cpucontrol->cpu
    no functional changes
2023-10-27 update diagrom from v54 to v61
2023-10-27 fix support of some ps/2 keyboards with slow clock
2023-10-28 update readme - add kempston bits info
2023-10-29 refactor memory controller; improve compatibility with NMOS Z80 CPUs; implement ULA+ registers reading
2023-10-29 fix int length in turbo modes (broken in 7039187)
2024-01-18 save extension board configuration
2024-01-19 implement fast forward
2024-01-28 handle external kempston joystick addon on zx-bus
2024-01-28 fix compatibility with some BDI addons
2024-07-21 fix compatibility with some BDI addons (2f83604f)
2024-10-02 add right+mode hotkey on joystick for fast-forward
